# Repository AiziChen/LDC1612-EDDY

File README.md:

# LDC1612 Eddy coil

A surface scanner for Klipper firmware [Eddy current probe](https://www.klipper3d.org/Eddy_Probe.html?h=eddy#eddy-current-inductive-probe) to provide very fast and high accuracy surface scanning.

## Features

* Similar to [Beacon revH](https://beacon3d.com/product/beacon-h/), but open source.
* Simple, no microcontroller, only LDC1612 chip inside.
* Connection stable, only support I2C connecting, but it is stable than via USB or CAN through an another MCU.
* Has an NTC thermistor to support coil temparature detect.

## How to use

This is a Kicad project, if you want to modify this project, you need to clone it, then download and install [Kicad](https://www.kicad.org/download/) to open.

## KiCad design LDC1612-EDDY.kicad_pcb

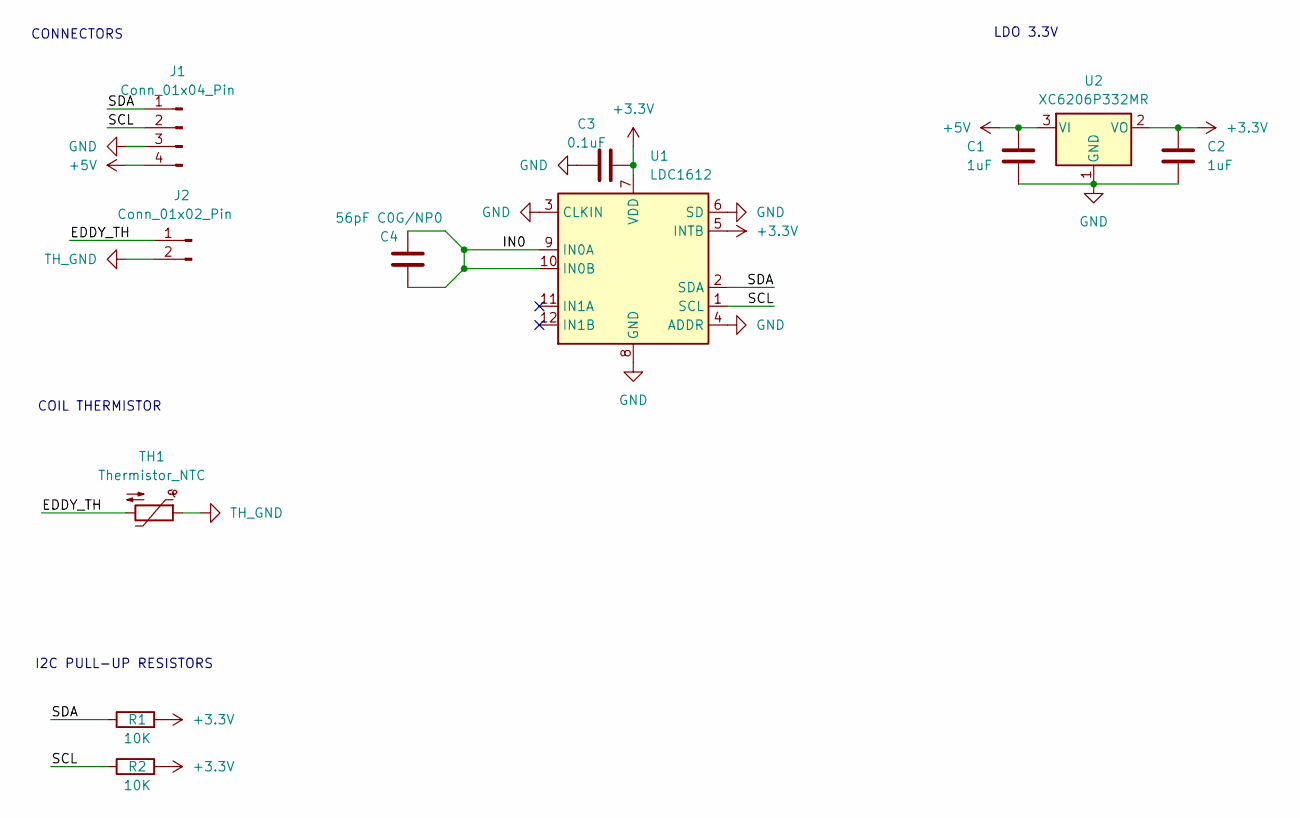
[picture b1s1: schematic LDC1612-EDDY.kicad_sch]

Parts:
C1, C2: 1uF; C_0402_1005Metric_Pad0.74x0.62mm_HandSolder
C3: 0.1uF; C_0402_1005Metric_Pad0.74x0.62mm_HandSolder
C4: 56pF C0G/NP0; C_0402_1005Metric
J1: Conn_01x04_Pin; JST_PH_B4B-PH-K_1x04_P2.00mm_Vertical
J2: Conn_01x02_Pin; JST_PH_B2B-PH-K_1x02_P2.00mm_Vertical
R1, R2: 10K; R_0402_1005Metric_Pad0.72x0.64mm_HandSolder
TH1: Thermistor_NTC; R_0603_1608Metric
U1: LDC1612; WSON-12-1EP_4x4mm_P0.5mm_EP2.6x3mm_ThermalVias
U2: XC6206P332MR; SOT-23-3

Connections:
+3.3V: C2.1, C3.2, R1.2, R2.2, U1.5 (INTB), U1.7 (VDD), U2.2 (VO)
+5V: C1.1, J1.4, U2.3 (VI)
/EDDY_TH: J2.1, TH1.2
/IN0: C4.1, C4.2, U1.9 (IN0A), U1.10 (IN0B)
/SCL: J1.2, R2.1, U1.1 (SCL)
/SDA: J1.1, R1.1, U1.2 (SDA)
GND: C1.2, C2.2, C3.1, J1.3, U1.3 (CLKIN), U1.4 (ADDR), U1.6 (SD), U1.8 (GND), U1.13 (GND), U2.1 (GND)
TH_GND: J2.2, TH1.1

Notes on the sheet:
LDO 3.3V
CONNECTORS
COIL THERMISTOR
I2C PULL-UP RESISTORS

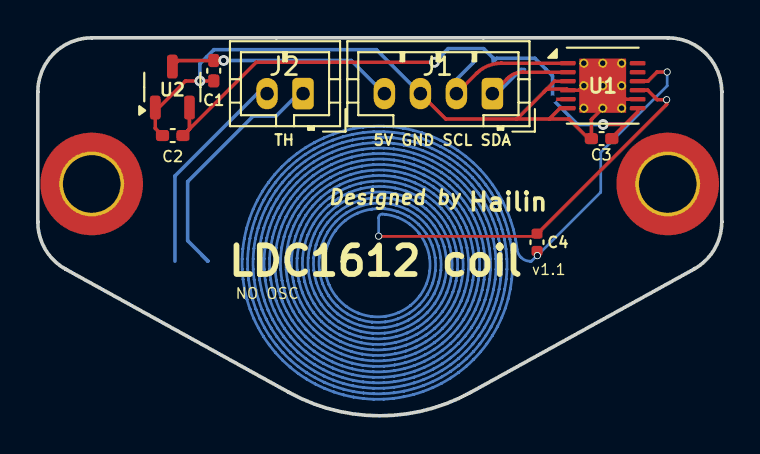
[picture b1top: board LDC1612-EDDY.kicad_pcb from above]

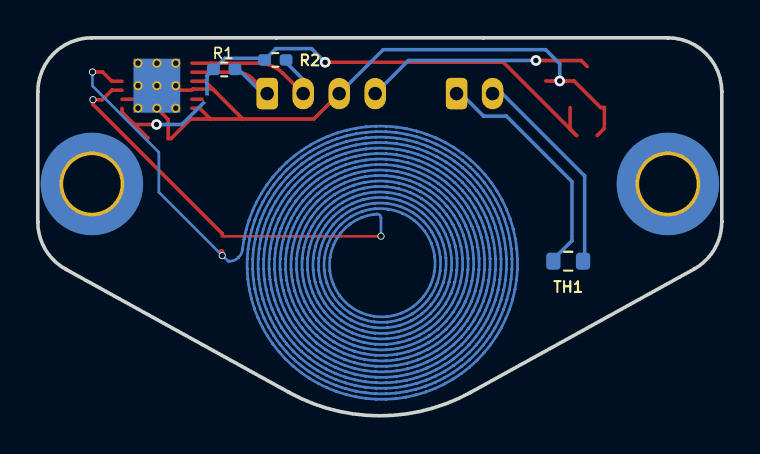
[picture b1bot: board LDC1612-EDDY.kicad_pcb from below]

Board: 2 copper layers, 38.0 x 21.0 mm, 11 parts (3 on the bottom side), 8 nets.

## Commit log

2025-08-15 added missing image
2025-08-15 README.md typo
2025-08-18 Schematic: add pull-up resistors for I2C SDA & SCL also make groups for different sections
2025-08-18 PCB: bump version to v1.02 * add pull-up resistors for SDA & SCL * change board name to `LDC1612 coil`
2025-08-20 Schematic & PCB: bump version to v1.1 * added an 12MHz external oscillator * fixed LDC1612 GND pin does not connected
2025-08-21 mod: add a STL mount for Voron carriage
2025-08-23 update mount carriage
    update images
2025-08-23 release no oscillator version
2025-08-23 update mount for carriage
